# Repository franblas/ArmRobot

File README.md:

# ArmRobot Project
The ArmRobot project aims to build and control a functional robotic arm using servo motors.
Project realized by Luc F. and Francois B. 

## The C library for STM32 card
A [C library](STM32/) has been developed to communicate with servo motors and control the arm as a whole through a STM32 electronic card.

## The Arduino library for Arduino card
An [Arduino](Arduino/) library has been developed to debug servo motors through an Arduino electronic card.

## Theorical code
A [Matlab](Matlab/) implementation has been done to compute equations for angles, based on the theory of Denhavit-Artenberg.

## Solidworks model
We have built the arm from scratch. [Here] (Solidworks/) you can find the whole model on solidworks we have realized, with every part of the arm.

## Joystick
Move an arm robot is cool, but with a joystick it's cooler ! [Here] (PCB_Joystick/) you can can find the pcb of the joystick, realized with Eagle.

## Project rapport
You can find the whole project rapport in pdf format [here] (https://github.com/franblas/ArmRobot/blob/master/Doc/compte_rendu_bras_de_robot.pdf?raw=true) (It's in french).

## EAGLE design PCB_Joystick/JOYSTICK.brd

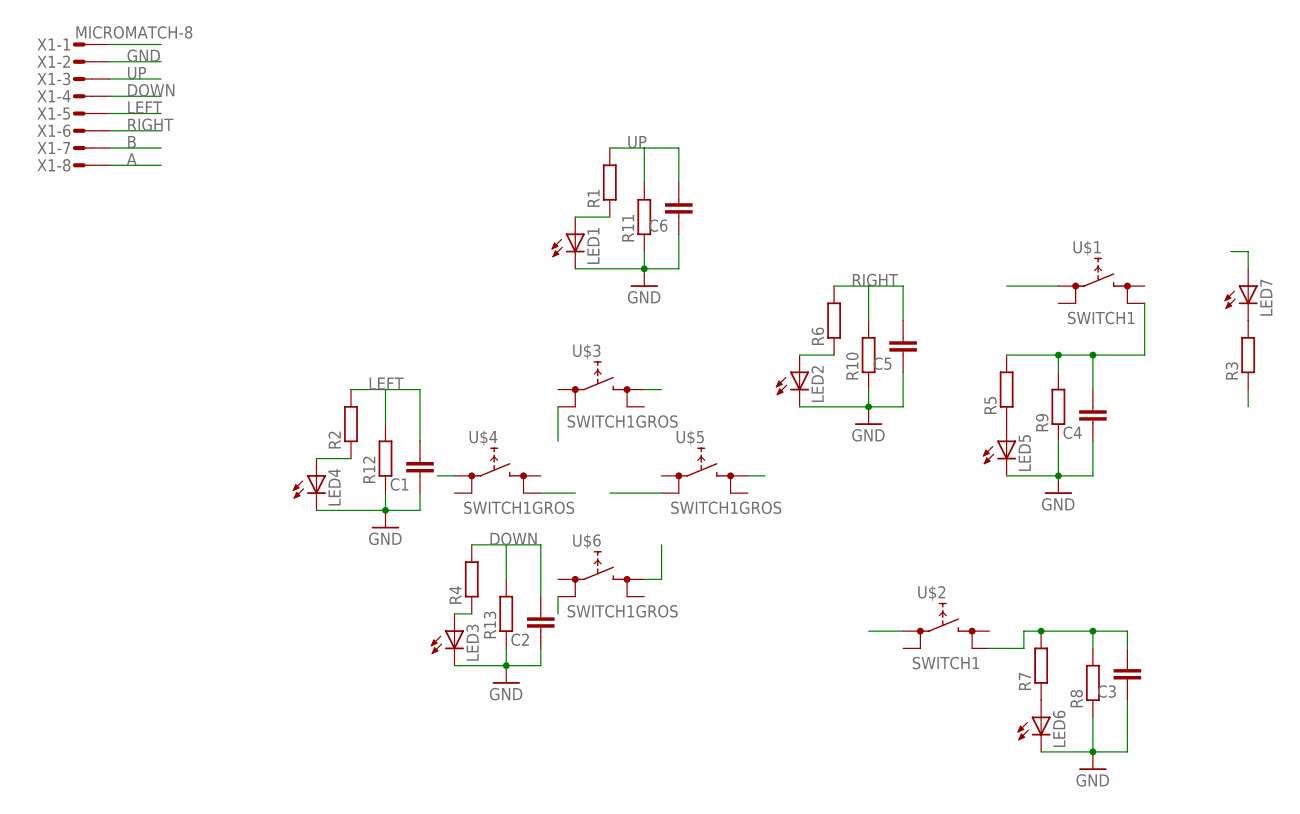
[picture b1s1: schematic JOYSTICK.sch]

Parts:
C1, C2, C3, C4, C5, C6: C-EUC0805; C0805
LED1, LED2, LED3, LED4, LED5, LED6, LED7: LED3MM
R1, R2, R3, R4, R5, R6, R7, R8, R9, R10, R11, R12, R13: R-EU_R0805; R0805
U$1, U$2: SWITCH1; TL1105
U$3, U$4, U$5, U$6: SWITCH1GROS; REKN
X1: MICROMATCH-8

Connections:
+5V: LED7.A, U$1.1 (0), U$2.1 (0), U$3.1B (0), U$4.2B (1), U$5.1B (0), U$6.2A (1), X1.1
A: C4.2, R5.2, R9.2, U$1.4 (1), X1.8
B: C3.2, R7.2, R8.2, U$2.4 (1), X1.7
DOWN: C2.2, R4.2, R13.2, U$6.1B (0), X1.4
GND: C1.1, C2.1, C3.1, C4.1, C5.1, C6.1, LED1.K (C), LED2.K (C), LED3.K (C), LED4.K (C), LED5.K (C), LED6.K (C), R3.1, R8.1, R9.1, R10.1, R11.1, R12.1, R13.1, X1.2
LEFT: C1.2, R2.2, R12.2, U$4.1A (0), X1.5
unnamed: LED1.A, R1.1
unnamed: LED4.A, R2.1
unnamed: LED7.K (C), R3.2
unnamed: LED3.A, R4.1
unnamed: LED5.A, R5.1
unnamed: LED2.A, R6.1
unnamed: LED6.A, R7.1
RIGHT: C5.2, R6.2, R10.2, U$5.2A (1), X1.6
UP: C6.2, R1.2, R11.2, U$3.2A (1), X1.3

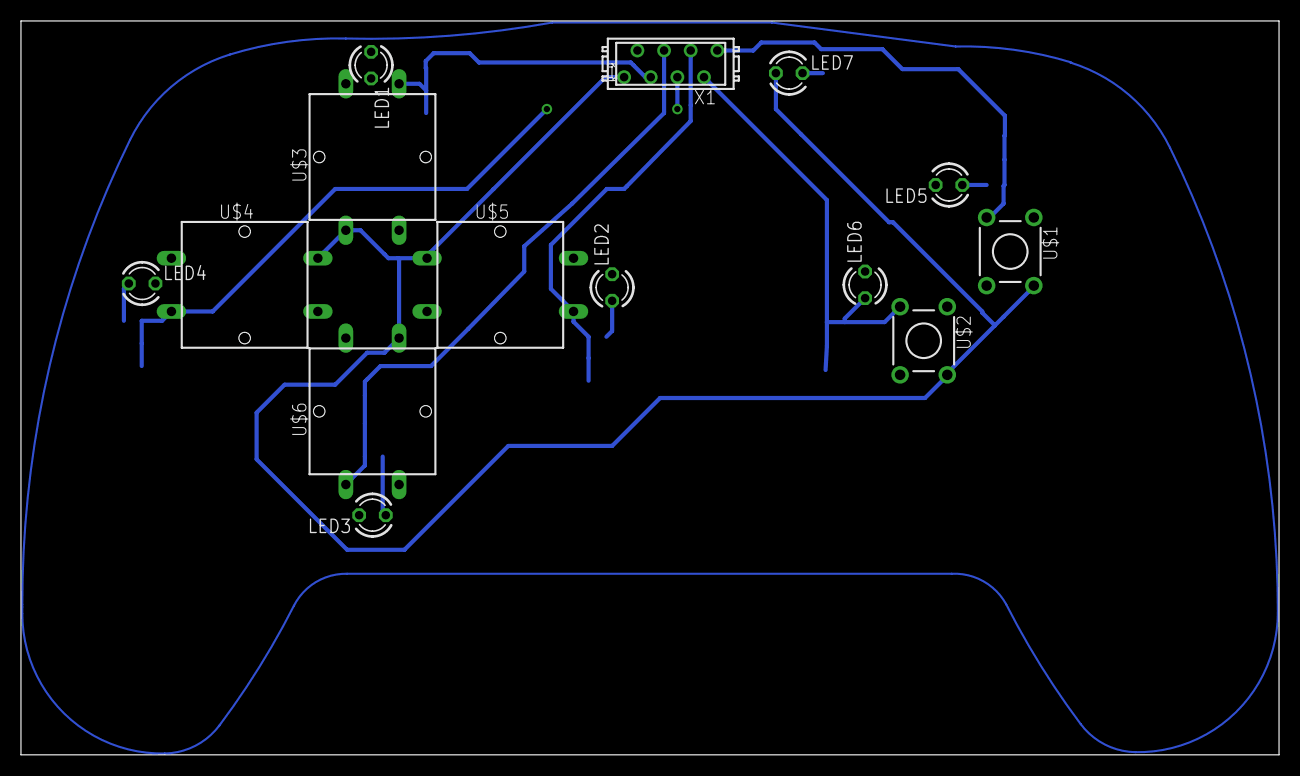
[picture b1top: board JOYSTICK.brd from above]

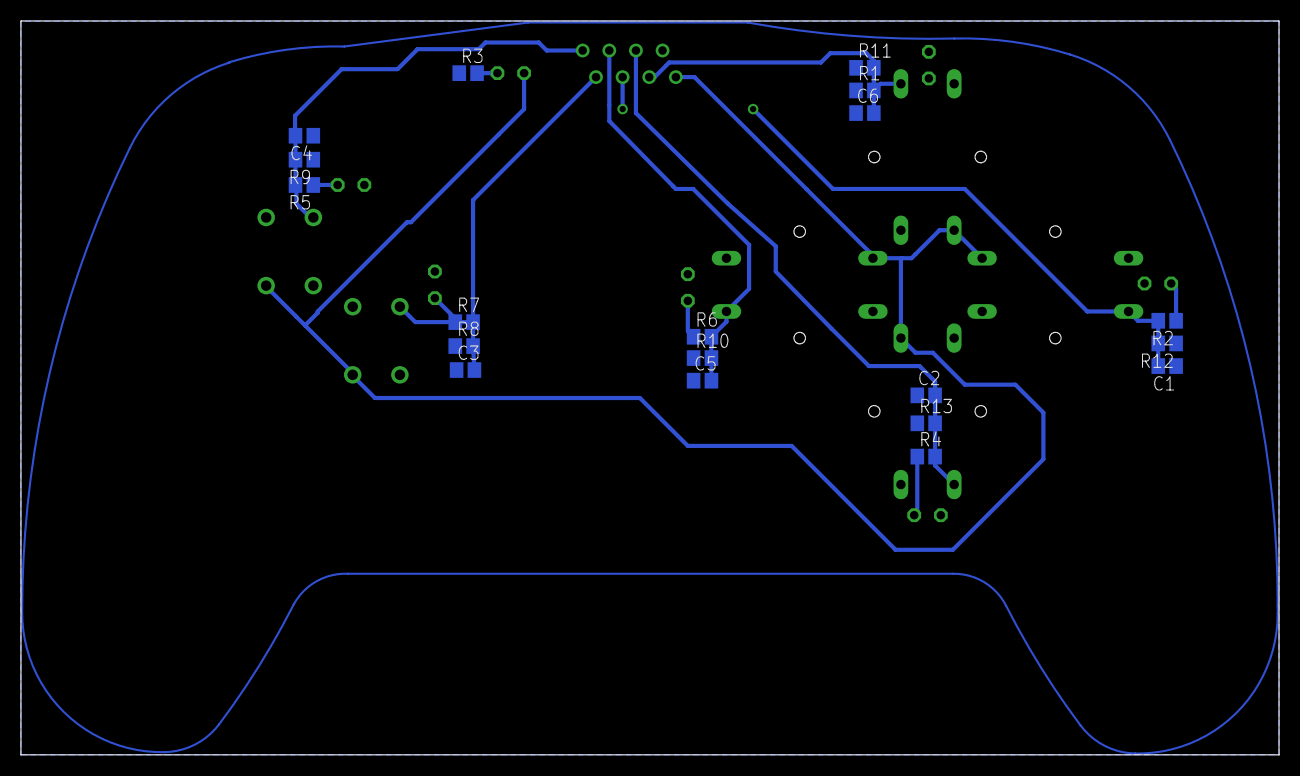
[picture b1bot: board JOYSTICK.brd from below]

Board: 2 copper layers, 120.0 x 70.0 mm, 33 parts (19 on the bottom side), 15 nets.

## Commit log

2014-11-11 electronics
2016-09-30 Create LICENSE
